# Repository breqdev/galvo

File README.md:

# Laser Vector Projector

Read the project writeup [here](https://breq.dev/projects/laser-projector)!

> This project is sponsored by PCBWay, who generously provided PCB fabrication services for this project. PCBWay provides high-quality boards with fast turnaround at low cost, and are a great option for both hobbyists and professionals.

Contained in this repository:

- [KiCAD Board Layout Files](board)
- [Bill of Materials](board/ESP32%20Galvo%20Driver.csv)
- [Firmware](galvo-firmware) -- you'll need to have the [Espressif toolchain](https://docs.espressif.com/projects/rust/book/getting-started/toolchain.html) installed to compile this
- [CAD files](cad) (SketchUp source files and STL)

Stuff not covered in the Bill of Materials:

- [RGB laser module and driver](https://www.aliexpress.us/item/3256810125144918.html)
- [Galvos with XY mount, driver, and power supply](https://www.aliexpress.us/item/3256809659931894.html)
- [Laser safety goggles](https://lasersafety.com/product/f42-p5l13-5000/)

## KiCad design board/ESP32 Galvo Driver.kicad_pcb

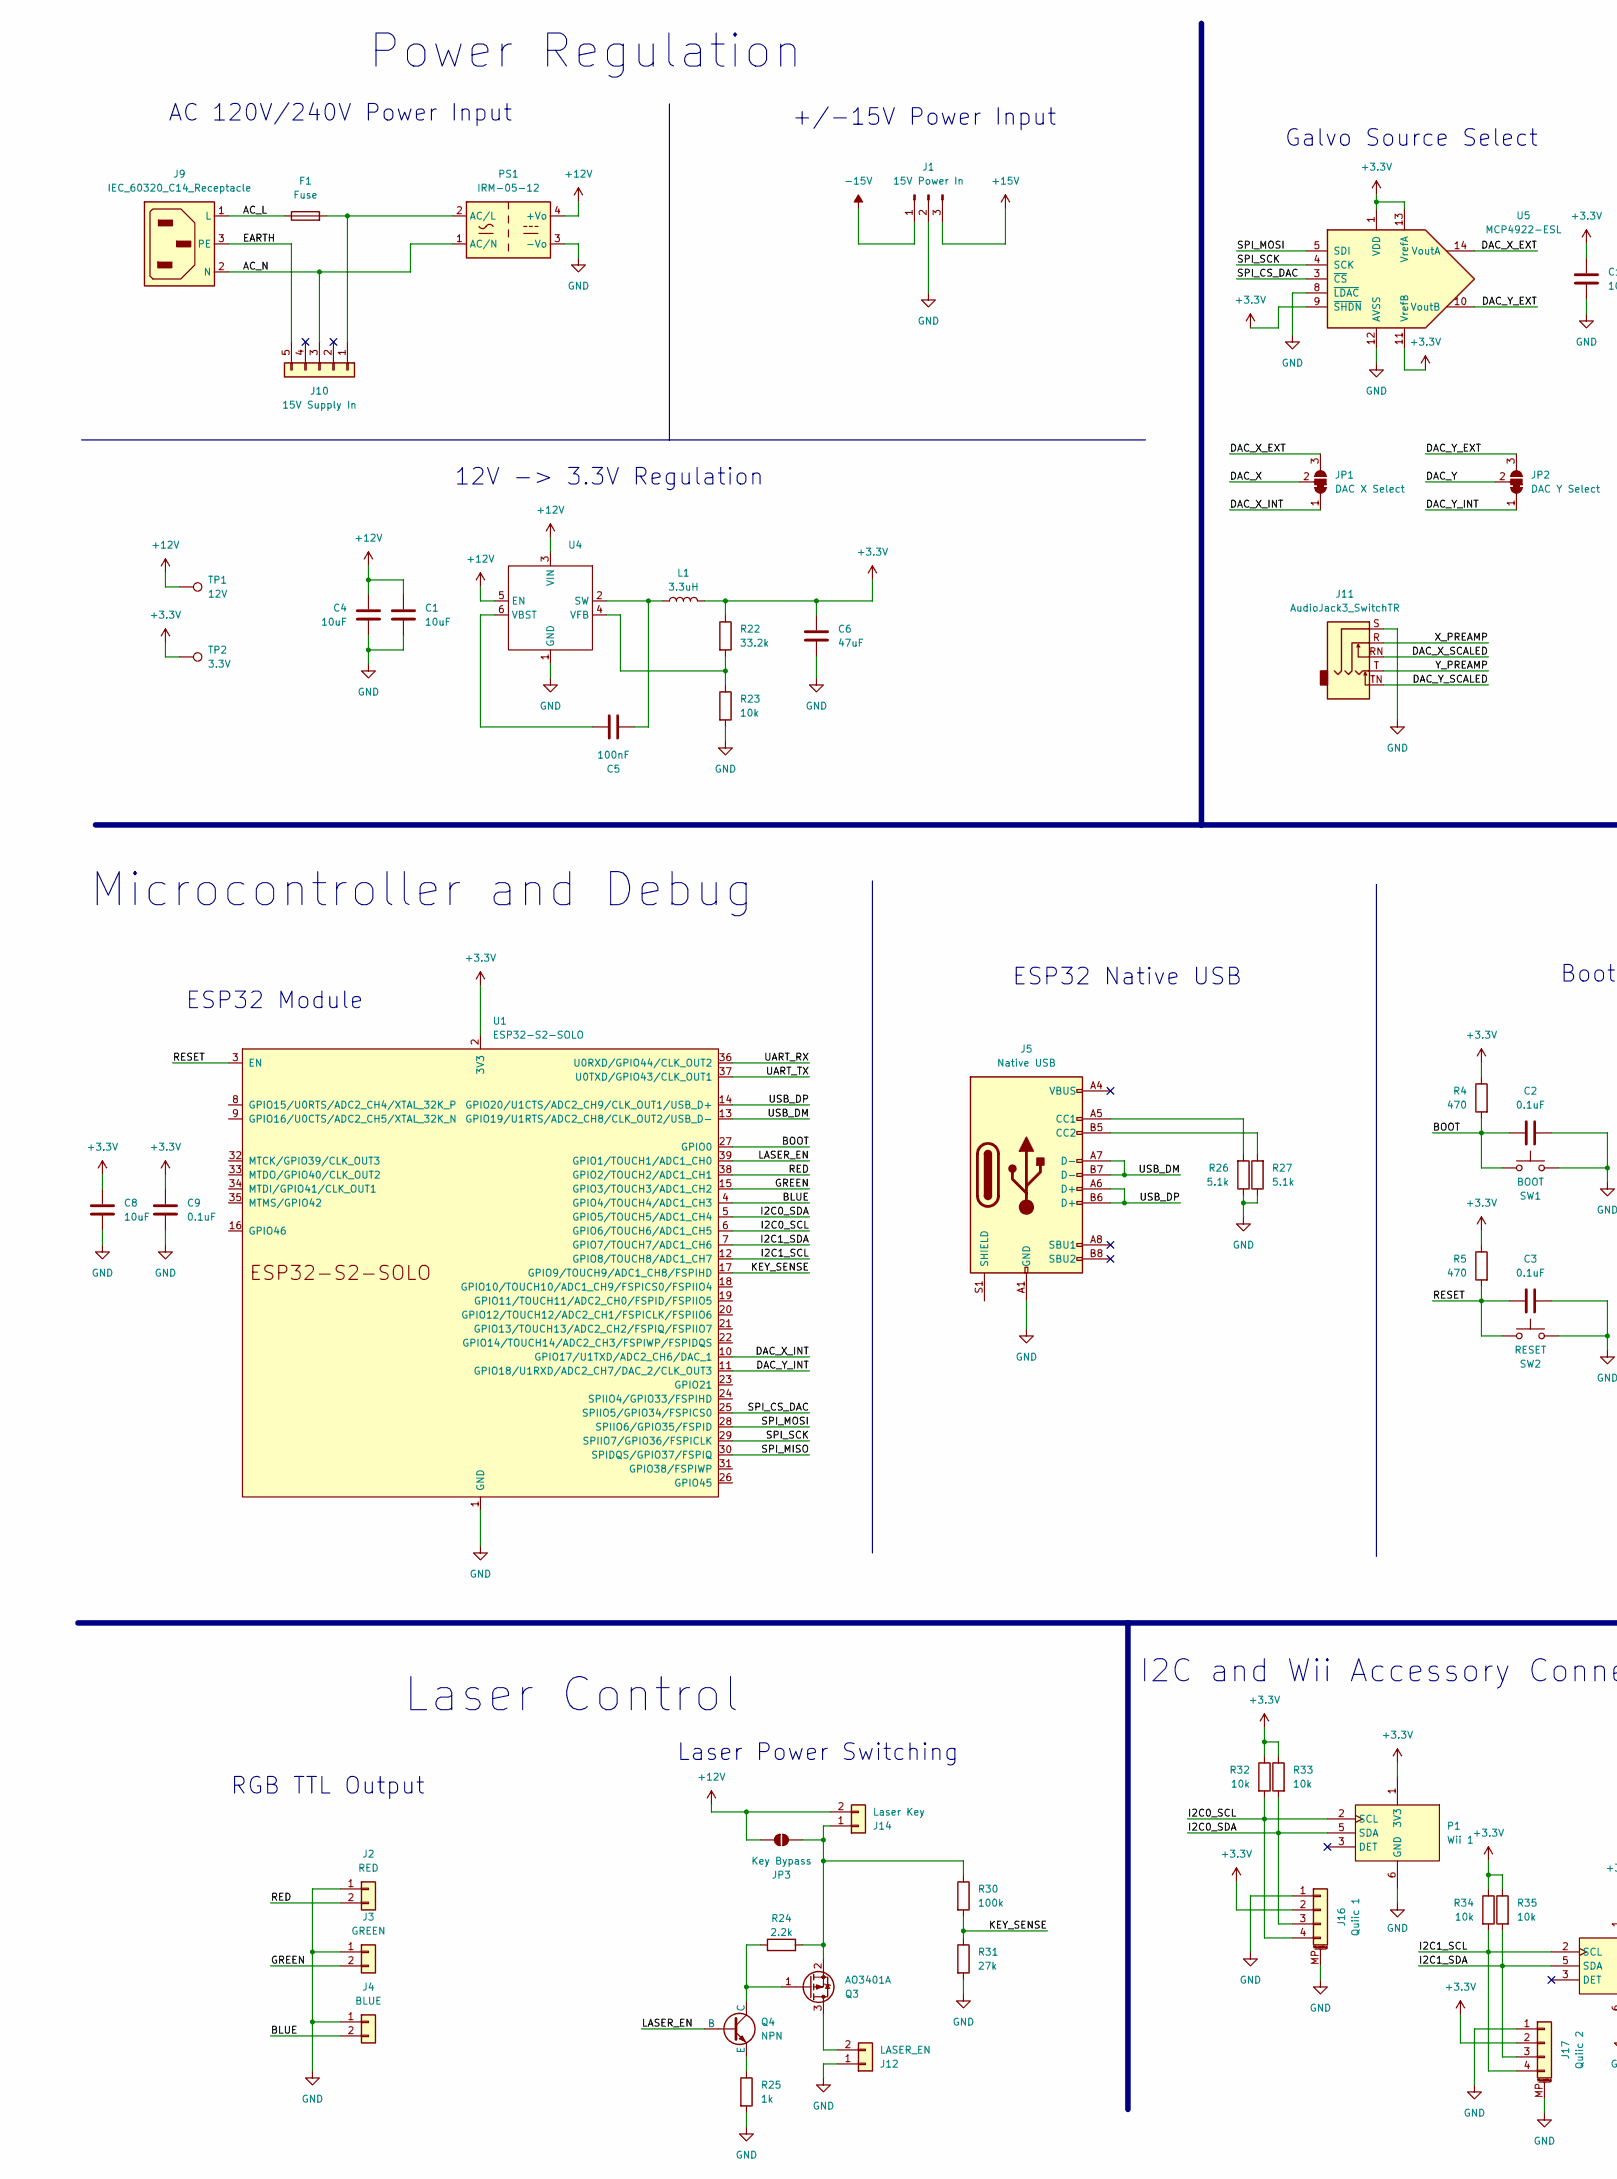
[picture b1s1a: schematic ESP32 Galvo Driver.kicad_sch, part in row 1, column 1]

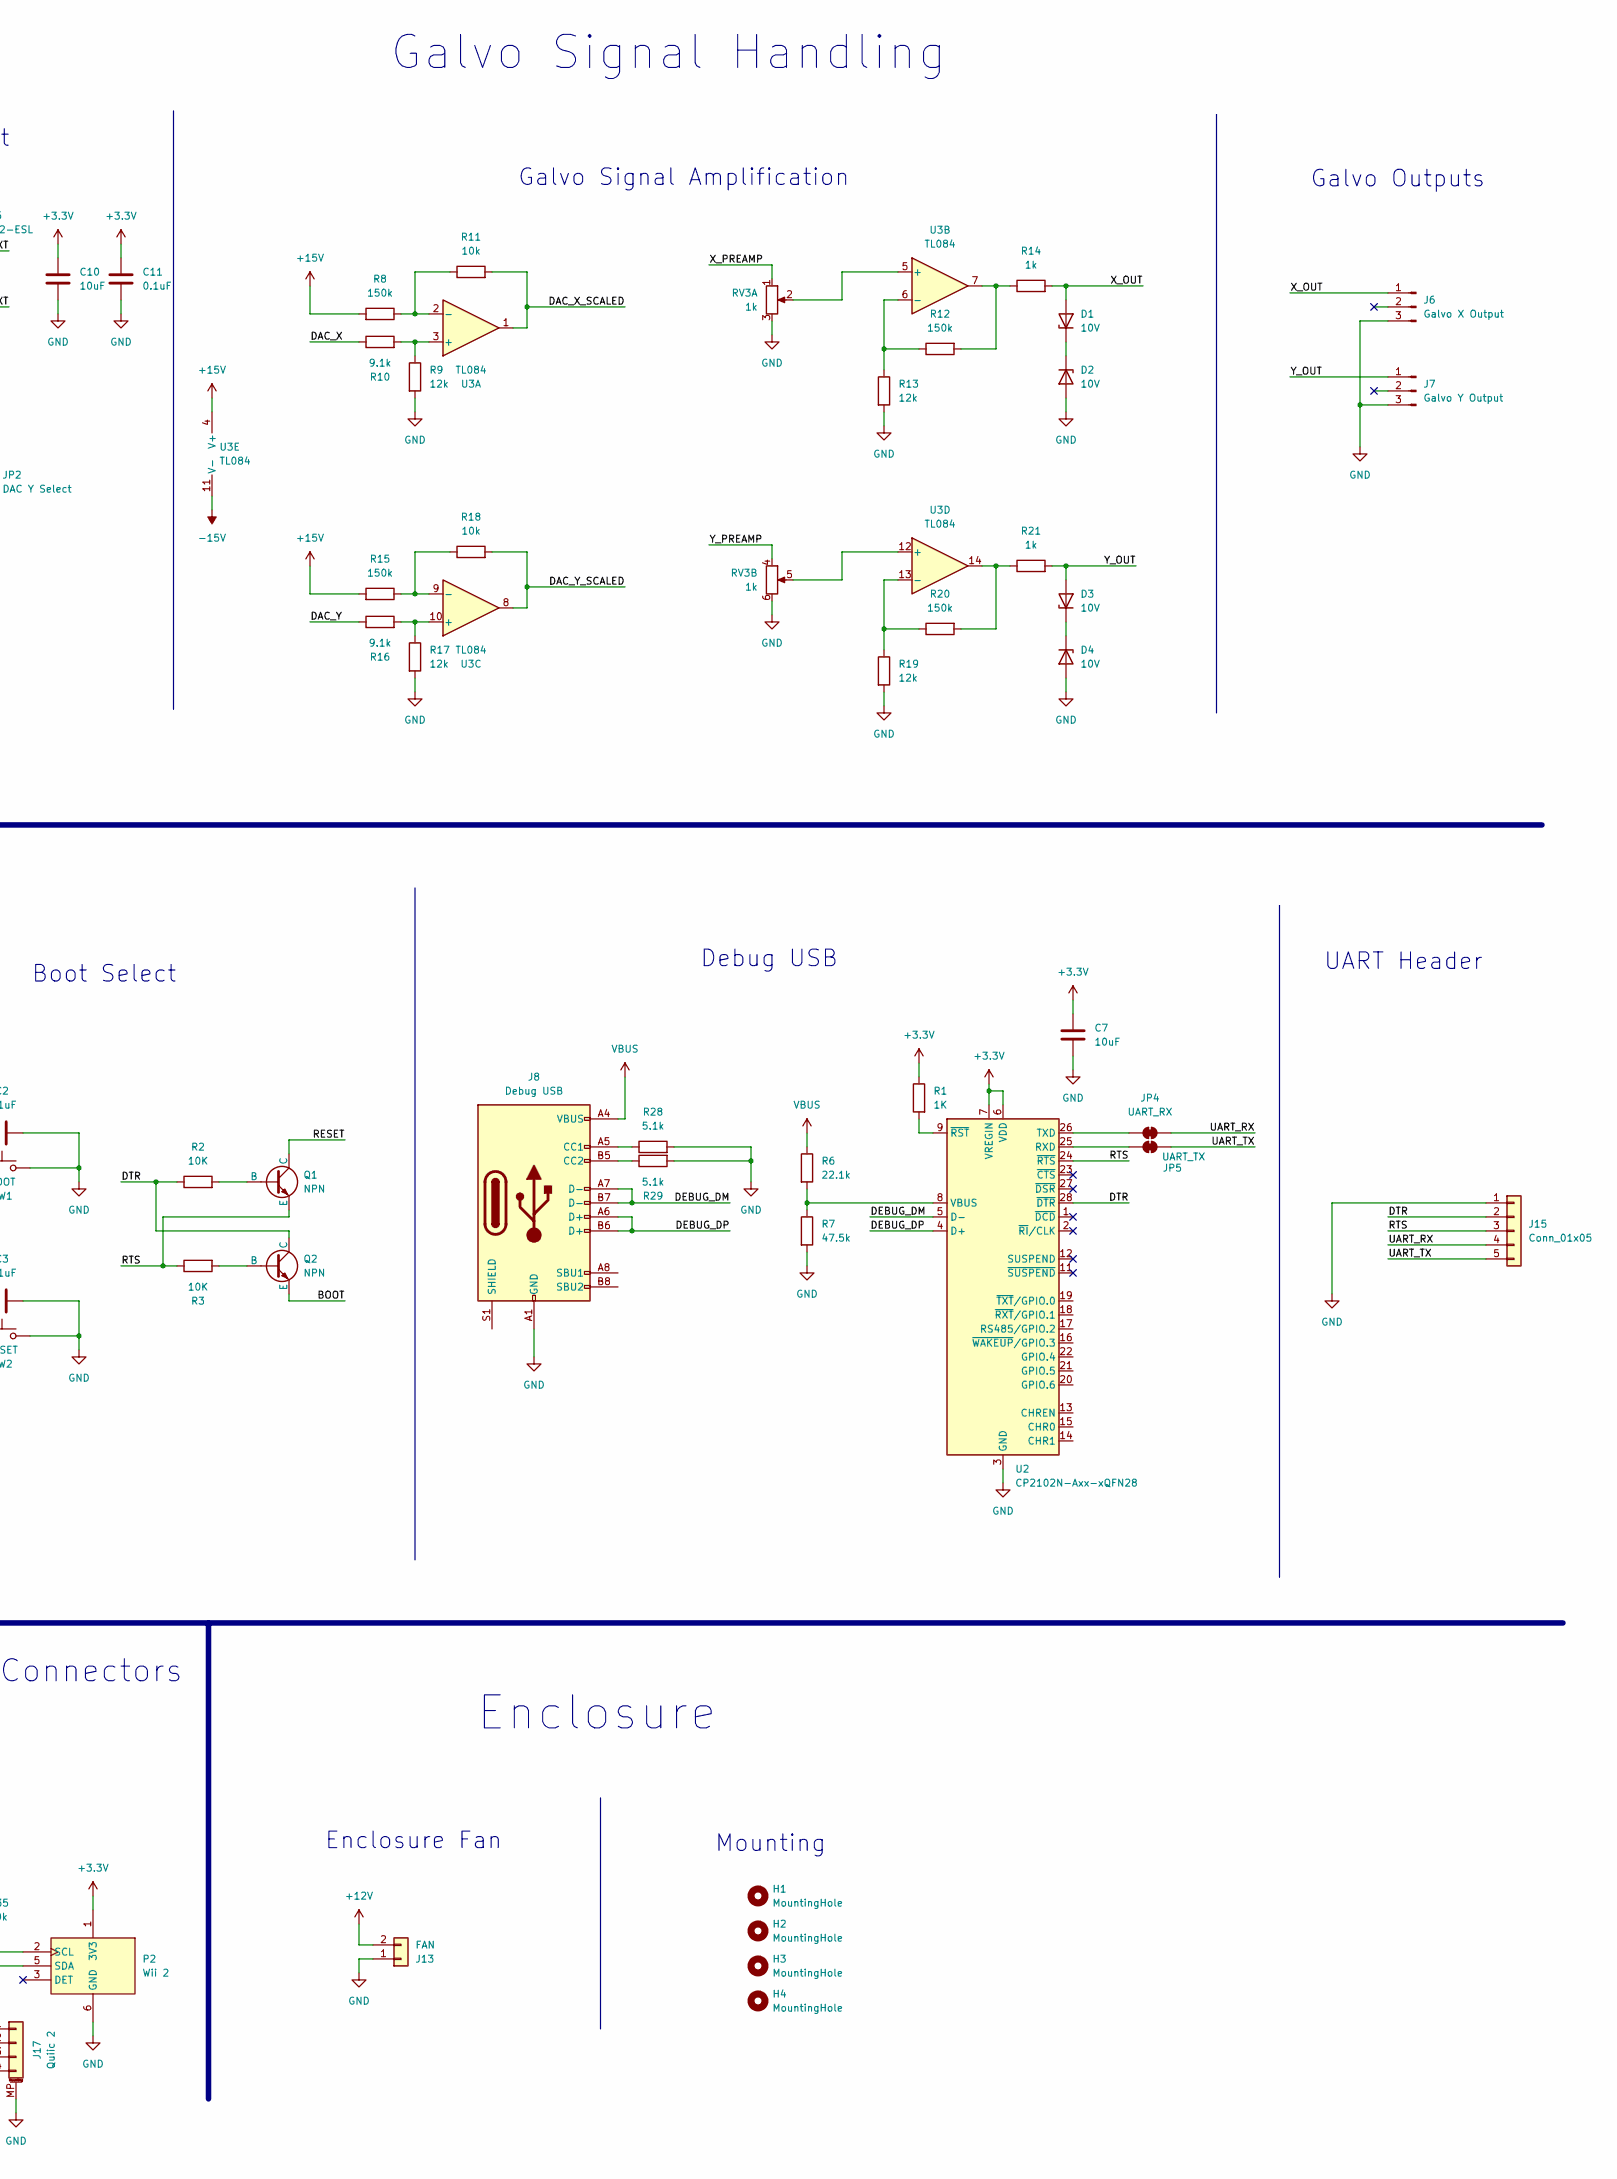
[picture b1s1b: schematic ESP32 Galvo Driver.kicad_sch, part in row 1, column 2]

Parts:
C1, C4, C7, C8, C10: 10uF; C_0603_1608Metric_Pad1.08x0.95mm_HandSolder
C2, C3, C9, C11: 0.1uF; C_0603_1608Metric_Pad1.08x0.95mm_HandSolder
C5: 100nF; C_0603_1608Metric_Pad1.08x0.95mm_HandSolder
C6: 47uF; C_0603_1608Metric_Pad1.08x0.95mm_HandSolder
D1, D2, D3, D4: 10V; D_SOD-123
F1: Fuse; Fuseholder_Clip-5x20mm_Littelfuse_111_Inline_P20.00x5.00mm_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
H1, H2, H3, H4: MountingHole; MountingHole_3.2mm_M3
J1: 15V Power In; Molex_KK-254_AE-6410-03A_1x03_P2.54mm_Vertical
J2: RED; JST_XH_B2B-XH-A_1x02_P2.50mm_Vertical
J3: GREEN; JST_XH_B2B-XH-A_1x02_P2.50mm_Vertical
J4: BLUE; JST_XH_B2B-XH-A_1x02_P2.50mm_Vertical
J5: Native USB; USB_C_Receptacle_GCT_USB4105-xx-A_16P_TopMnt_Horizontal
J6: Galvo X Output; JST_XH_B3B-XH-A_1x03_P2.50mm_Vertical
J7: Galvo Y Output; JST_XH_B3B-XH-A_1x03_P2.50mm_Vertical
J8: Debug USB; USB_C_Receptacle_GCT_USB4105-xx-A_16P_TopMnt_Horizontal
J9: IEC_60320_C14_Receptacle; QUALTEK_703W-00_52
J10: 15V Supply In; Molex_KK-396_5273-05A_1x05_P3.96mm_Vertical
J11: AudioJack3_SwitchTR; Jack_3.5mm_CUI_SJ1-3525N_Horizontal
J12: LASER_EN; JST_XH_B2B-XH-A_1x02_P2.50mm_Vertical
J13: FAN; JST_XH_B2B-XH-A_1x02_P2.50mm_Vertical
J14: Laser Key; JST_XH_B2B-XH-A_1x02_P2.50mm_Vertical
J15: Conn_01x05; PinHeader_1x05_P2.54mm_Vertical
J16: Quiic 1; JST_SH_BM04B-SRSS-TB_1x04-1MP_P1.00mm_Vertical
J17: Quiic 2; JST_SH_BM04B-SRSS-TB_1x04-1MP_P1.00mm_Vertical
JP1: DAC X Select; SolderJumper-3_P1.3mm_Bridged12_RoundedPad1.0x1.5mm
JP2: DAC Y Select; SolderJumper-3_P1.3mm_Bridged12_RoundedPad1.0x1.5mm
JP3: Key Bypass; SolderJumper-2_P1.3mm_Open_TrianglePad1.0x1.5mm
JP4: UART_RX; SolderJumper-2_P1.3mm_Bridged_Pad1.0x1.5mm
JP5: UART_TX; SolderJumper-2_P1.3mm_Bridged_Pad1.0x1.5mm
L1: 3.3uH; L_0805_2012Metric_Pad1.15x1.40mm_HandSolder
P1: Wii 1; Nintendo_Wii_Peripheral_5Pin_Card_edge
P2: Wii 2; Nintendo_Wii_Peripheral_5Pin_Card_edge
PS1: IRM-05-12; Converter_ACDC_MeanWell_IRM-05-xx_THT
Q1, Q2, Q4: NPN; SOT-23-3
Q3: AO3401A; SOT-23
R1: 1K; R_0603_1608Metric_Pad0.98x0.95mm_HandSolder
R2, R3: 10K; R_0603_1608Metric_Pad0.98x0.95mm_HandSolder
R4, R5: 470; R_0603_1608Metric_Pad0.98x0.95mm_HandSolder
R6: 22.1k; R_0603_1608Metric_Pad0.98x0.95mm_HandSolder
R7: 47.5k; R_0603_1608Metric_Pad0.98x0.95mm_HandSolder
R8, R12, R15, R20: 150k; R_0603_1608Metric_Pad0.98x0.95mm_HandSolder
R9, R13, R17, R19: 12k; R_0603_1608Metric_Pad0.98x0.95mm_HandSolder
R10, R16: 9.1k; R_0603_1608Metric_Pad0.98x0.95mm_HandSolder
R11, R18, R23, R32, R33, R34, R35: 10k; R_0603_1608Metric_Pad0.98x0.95mm_HandSolder
R14, R21, R25: 1k; R_0603_1608Metric_Pad0.98x0.95mm_HandSolder
R22: 33.2k; R_0603_1608Metric_Pad0.98x0.95mm_HandSolder
R24: 2.2k; R_0603_1608Metric_Pad0.98x0.95mm_HandSolder
R26, R27, R28, R29: 5.1k; R_0603_1608Metric_Pad0.98x0.95mm_HandSolder
R30: 100k; R_0603_1608Metric_Pad0.98x0.95mm_HandSolder
R31: 27k; R_0603_1608Metric_Pad0.98x0.95mm_HandSolder
RV3: 1k; Potentiometer_Alps_RK163_Dual_Horizontal
SW1: BOOT; SW_Tactile_SPST_Angled_PTS645Vx58-2LFS
SW2: RESET; SW_Tactile_SPST_Angled_PTS645Vx58-2LFS
TP1: 12V; TestPoint_Pad_D2.5mm
TP2: 3.3V; TestPoint_Pad_D2.5mm
U1: ESP32-S2-SOLO
U2: CP2102N-Axx-xQFN28; QFN-28-1EP_5x5mm_P0.5mm_EP3.35x3.35mm
U3: TL084; SOIC-14_3.9x8.7mm_P1.27mm
U4: SOT-23-6_Handsoldering
U5: MCP4922-ESL; SOIC-14_3.9x8.7mm_P1.27mm

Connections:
+3.3V: C6.1, C7.1, C8.1, C9.1, C10.1, C11.1, J16.2, J17.2, L1.2, P1.1 (3V3), P2.1 (3V3), R1.1, R4.1, R5.1, R22.1, R32.1, R33.1, R34.1, R35.1, TP2.1 (1_1), U1.2 (3V3), U2.6 (VDD), U2.7 (VREGIN), U5.1 (VDD), U5.9 (~SHDN), U5.11 (VrefB), U5.13 (VrefA)
+12V: C1.1, C4.1, J13.2, J14.2, JP3.1 (A), PS1.4 (+Vo), TP1.1 (1_1), U4.3 (VIN), U4.5 (EN)
+15V: J1.3, R8.2, R15.2, U3.4 (V+)
-15V: J1.1, U3.11 (V-)
/AC_L: F1.1, J9.1 (L)
/AC_N: J9.2 (N), J10.3, PS1.1 (AC/N)
/BLUE: J4.2, U1.4 (GPIO4/TOUCH4/ADC1_CH3)
/BOOT: C2.1, Q2.3 (E), R4.2, SW1.2, U1.27 (GPIO0)
/DAC_X: JP1.2 (C), R10.1
/DAC_X_EXT: JP1.3 (B), U5.14 (VoutA)
/DAC_X_INT: JP1.1 (A), U1.10 (GPIO17/U1TXD/ADC2_CH6/DAC_1)
/DAC_X_SCALED: J11.RN, R11.2, U3.1
/DAC_Y: JP2.2 (C), R16.1
/DAC_Y_EXT: JP2.3 (B), U5.10 (VoutB)
/DAC_Y_INT: JP2.1 (A), U1.11 (GPIO18/U1RXD/ADC2_CH7/DAC_2/CLK_OUT3)
/DAC_Y_SCALED: J11.TN, R18.2, U3.8
/DEBUG_DM: J8.A7 (D-), J8.B7 (D-), U2.5 (D-)
/DEBUG_DP: J8.A6 (D+), J8.B6 (D+), U2.4 (D+)
/DTR: J15.2, Q2.1 (C), R2.1, U2.28 (~DTR)
/EARTH: J9.3 (PE), J10.5
/GREEN: J3.2, U1.15 (GPIO3/TOUCH3/ADC1_CH2)
/I2C0_SCL: J16.4, P1.2 (SCL), R32.2, U1.6 (GPIO6/TOUCH6/ADC1_CH5)
/I2C0_SDA: J16.3, P1.5 (SDA), R33.2, U1.5 (GPIO5/TOUCH5/ADC1_CH4)
/I2C1_SCL: J17.4, P2.2 (SCL), R34.2, U1.12 (GPIO8/TOUCH8/ADC1_CH7)
/I2C1_SDA: J17.3, P2.5 (SDA), R35.2, U1.7 (GPIO7/TOUCH7/ADC1_CH6)
/KEY_SENSE: R30.2, R31.1, U1.17 (GPIO9/TOUCH9/ADC1_CH8/FSPIHD)
/LASER_EN: Q4.2 (B), U1.39 (GPIO1/TOUCH1/ADC1_CH0)
/RED: J2.2, U1.38 (GPIO2/TOUCH2/ADC1_CH1)
/RESET: C3.1, Q1.1 (C), R5.2, SW2.2, U1.3 (EN)
/RTS: J15.3, Q1.3 (E), R3.1, U2.24 (~RTS)
/SPI_CS_DAC: U1.25 (SPIIO5/GPIO34/FSPICS0), U5.3 (~CS)
/SPI_MISO: U1.30 (SPIDQS/GPIO37/FSPIQ)
/SPI_MOSI: U1.28 (SPIIO6/GPIO35/FSPID), U5.5 (SDI)
/SPI_SCK: U1.29 (SPIIO7/GPIO36/FSPICLK), U5.4 (SCK)
/UART_RX: J15.4, JP4.2 (B), U1.36 (U0RXD/GPIO44/CLK_OUT2)
/UART_TX: J15.5, JP5.2 (B), U1.37 (U0TXD/GPIO43/CLK_OUT1)
/USB_DM: J5.A7 (D-), J5.B7 (D-), U1.13 (GPIO19/U1RTS/ADC2_CH8/CLK_OUT2/USB_D-)
/USB_DP: J5.A6 (D+), J5.B6 (D+), U1.14 (GPIO20/U1CTS/ADC2_CH9/CLK_OUT1/USB_D+)
/X_OUT: D1.2 (A), J6.1, R14.2
/X_PREAMP: J11.R, RV3.1
/Y_OUT: D3.2 (A), J7.1, R21.2
/Y_PREAMP: J11.T, RV3.4
GND: C1.2, C2.2, C3.2, C4.2, C6.2, C7.2, C8.2, C9.2, C10.2, C11.2, D2.2 (A), D4.2 (A), J1.2, J2.1, J3.1, J4.1, J5.A1 (GND), J5.A12 (GND), J5.B1 (GND), J5.B12 (GND), J6.3, J7.3, J8.A1 (GND), J8.A12 (GND), J8.B1 (GND), J8.B12 (GND), J11.S, J12.1, J13.1, J15.1, J16.1, J16.MP (MountPin), J17.1, J17.MP (MountPin), P1.6 (GND), P2.6 (GND), PS1.3 (-Vo), R7.2, R9.2, R13.2, R17.2, R19.2, R23.2, R25.2, R26.1, R27.1, R28.2, R29.2, R31.2, RV3.3, RV3.6, SW1.1, SW2.1, U1.1 (GND), U1.40 (GND), U1.41 (GND), U2.3 (GND), U2.29 (GND), U4.1 (GND), U5.8 (~LDAC), U5.12 (AVSS)
unnamed: D1.1 (K), D2.1 (K)
unnamed: D3.1 (K), D4.1 (K)
unnamed: J5.A5 (CC1), R26.2
unnamed: J5.B5 (CC2), R27.2
unnamed: J8.A5 (CC1), R28.1
unnamed: J8.B5 (CC2), R29.1
unnamed: F1.2, J10.1, PS1.2 (AC/L)
unnamed: J12.2, Q3.3 (D)
unnamed: J14.1, JP3.2 (B), Q3.2 (S), R24.2, R30.1
unnamed: JP4.1 (A), U2.26 (TXD)
unnamed: JP5.1 (A), U2.25 (RXD)
unnamed: Q1.2 (B), R2.2
unnamed: Q2.2 (B), R3.2
unnamed: Q3.1 (G), Q4.1 (C), R24.1
unnamed: Q4.3 (E), R25.1
unnamed: R12.2, R14.1, U3.7
unnamed: R20.2, R21.1, U3.14
unnamed: R6.2, R7.1, U2.8 (VBUS)
unnamed: R1.2, U2.9 (~RST)
unnamed: R9.1, R10.2, U3.3 (+)
unnamed: R8.1, R11.1, U3.2 (-)
unnamed: RV3.2, U3.5 (+)
unnamed: R12.1, R13.1, U3.6 (-)
unnamed: R16.2, R17.1, U3.10 (+)
unnamed: R15.1, R18.1, U3.9 (-)
unnamed: RV3.5, U3.12 (+)
unnamed: R19.1, R20.1, U3.13 (-)
unnamed: C5.2, L1.1, U4.2 (SW)
unnamed: C5.1, U4.6 (VBST)
unnamed: R22.2, R23.1, U4.4 (VFB)
VBUS: J8.A4 (VBUS), J8.A9 (VBUS), J8.B4 (VBUS), J8.B9 (VBUS), R6.1

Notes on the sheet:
Power Regulation
Enclosure
ESP32 Native USB
Microcontroller and Debug
AC 120V/240V Power Input
12V -> 3.3V Regulation
UART Header
RGB TTL Output
Laser Power Switching
Galvo Signal Handling
Boot Select
ESP32 Module
Enclosure Fan
I2C and Wii Accessory Connectors
Mounting
Laser Control
Galvo Source Select
+/-15V Power Input
Debug USB
Galvo Signal Amplification
Galvo Outputs

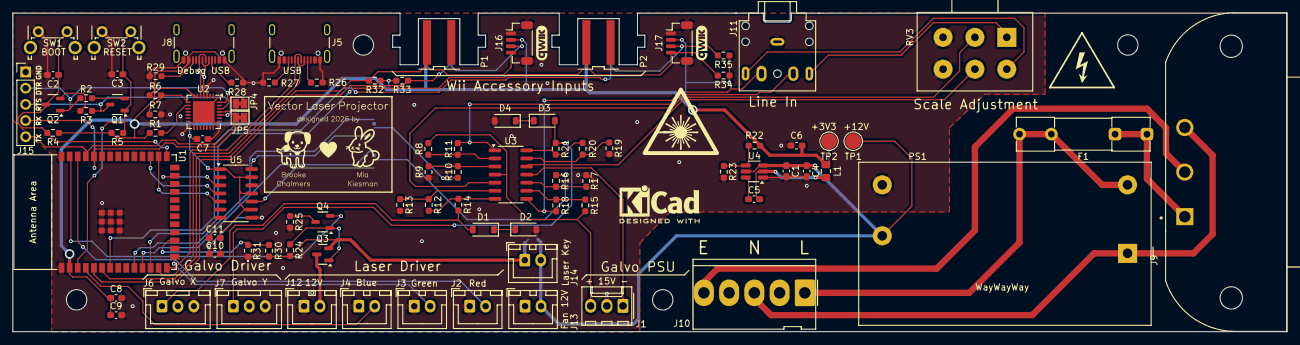
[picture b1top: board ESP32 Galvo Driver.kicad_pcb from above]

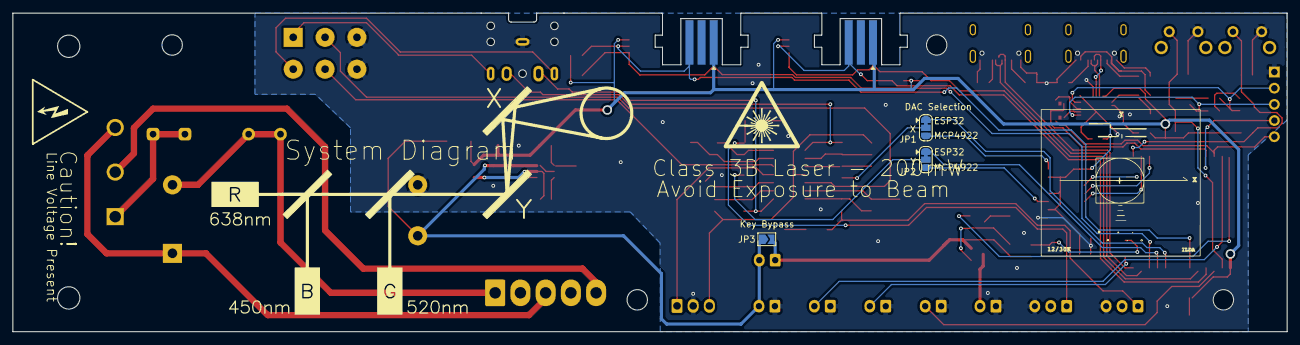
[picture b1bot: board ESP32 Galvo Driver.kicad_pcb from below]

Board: 2 copper layers, 199.9 x 50.0 mm, 95 parts (3 on the bottom side), 73 nets.

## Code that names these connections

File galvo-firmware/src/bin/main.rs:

#![no_std]
#![no_main]
#![deny(
    clippy::mem_forget,
    reason = "mem::forget is generally not safe to do with esp_hal types, especially those \
    holding buffers for the duration of a data transfer."
)]

use alloc::boxed::Box;
use alloc::string::String;
use alloc::vec::Vec;
use embassy_executor::Spawner;
use embassy_net::{DhcpConfig, StackResources};
use embassy_time::{Duration, Timer};
use esp_backtrace as _;
use esp_hal::clock::CpuClock;
use esp_hal::delay::Delay;
use esp_hal::i2c::master::{Config, I2c};
use esp_hal::ledc::timer::TimerIFace;
use esp_hal::ledc::{Ledc, LowSpeed, timer};
use esp_hal::otg_fs::{Usb, UsbBus};
use esp_hal::peripherals;
use esp_hal::rng::Rng;
use esp_hal::rtc_cntl::Rtc;
use esp_hal::time::Rate;
use esp_hal::timer::timg::TimerGroup;
use esp_radio::Controller;
use galvo_driver::controls::parse_report;
use galvo_driver::network::{
    RtcTimeSource, SharedRtc, connection, get_mastodon_status, get_time_ntp, net_task,
};
use galvo_driver::protocol::{Command, Response};
use usb_device::prelude::{UsbDeviceBuilder, UsbVidPid};
use usbd_serial::{SerialPort, USB_CLASS_CDC};
use vector_apps::apps::clock::Clock;
use vector_apps::apps::svg::SvgApp;
use vector_apps::apps::{self, Controls, VectorApp};
use wii_accessories::WiiAccessory;

use log::info;

use embassy_sync::blocking_mutex::Mutex;
use galvo_driver::lasers::Lasers;
use galvo_driver::led::IndicatorLed;
use vector_apps::apps::align::Align;
use vector_apps::apps::alphabet::AlphabetDemo;
use vector_apps::apps::asteroids::Asteroids;
use vector_apps::apps::cube::CubeDemo;
use vector_apps::apps::cycle::Cycle;
use vector_apps::apps::ilda::Ilda;
use vector_apps::apps::maps::Maps;

extern crate alloc;

// This creates a default app-descriptor required by the esp-idf bootloader.
// For more information see: <https://docs.espressif.com/projects/esp-idf/en/stable/esp32/api-reference/system/app_image_format.html#application-description>
esp_bootloader_esp_idf::esp_app_desc!();

// When you are okay with using a nightly compiler it's better to use https://docs.rs/static_cell/2.1.0/static_cell/macro.make_static.html
macro_rules! mk_static {
    ($t:ty,$val:expr) => {{
        static STATIC_CELL: static_cell::StaticCell<$t> = static_cell::StaticCell::new();
        #[deny(unused_attributes)]
        let x = STATIC_CELL.uninit().write(($val));
        x
    }};
}

static mut EP_MEMORY: [u32; 1024] = [0; 1024];

#[esp_rtos::main]
async fn main(spawner: Spawner) -> ! {
    // generator version: 1.0.1

    esp_println::logger::init_logger_from_env();

    let config = esp_hal::Config::default().with_cpu_clock(CpuClock::max());
    let peripherals = esp_hal::init(config);

    esp_alloc::heap_allocator!(#[esp_hal::ram(reclaimed)] size: 139264);

    let timg0 = TimerGroup::new(peripherals.TIMG0);
    esp_rtos::start(timg0.timer0);

    info!("Embassy initialized!");

    let delay = Delay::new();

    let ledc = Ledc::new(peripherals.LEDC);
    let mut timer = ledc.timer::<LowSpeed>(timer::Number::Timer0);
    timer
        .configure(timer::config::Config {
            duty: timer::config::Duty::Duty8Bit,
            clock_source: timer::LSClockSource::APBClk,
            frequency: Rate::from_khz(24),
        })
        .unwrap();

    let mut lasers = Lasers::new(
        peripherals.GPIO1,
        peripherals.GPIO9,
        peripherals.GPIO2,
        peripherals.GPIO3,
        peripherals.GPIO4,
        ledc,
        &timer,
        peripherals.DAC2,
        peripherals.GPIO18,
        peripherals.DAC1,
        peripherals.GPIO17,
    );

    let mut controls_p1 = {
        let i2c = I2c::new(peripherals.I2C0, Config::default())
            .unwrap()
            .with_sda(peripherals.GPIO5)
            .with_scl(peripherals.GPIO6);

        WiiAccessory::new(i2c)
    };
    let mut controls_p2 = {
        let i2c = I2c::new(peripherals.I2C1, Config::default())
            .unwrap()
            .with_sda(peripherals.GPIO7)
            .with_scl(peripherals.GPIO8);

        WiiAccessory::new(i2c)
    };

    let usb = Usb::new(peripherals.USB0, peripherals.GPIO20, peripherals.GPIO19);
    let usb_bus = UsbBus::new(usb, unsafe { &mut *core::ptr::addr_of_mut!(EP_MEMORY) });

    let mut serial = SerialPort::new(&usb_bus);

    let mut usb_dev = UsbDeviceBuilder::new(&usb_bus, UsbVidPid(0x303A, 0x3001))
        .device_class(USB_CLASS_CDC)
        .build();

    let rtc = mk_static!(SharedRtc, Mutex::new(Rtc::new(peripherals.LPWR)));

    let esp_radio_ctrl = &*mk_static!(Controller<'static>, esp_radio::init().unwrap());

    let (controller, interfaces) =
        esp_radio::wifi::new(esp_radio_ctrl, peripherals.WIFI, Default::default()).unwrap();

    let wifi_interface = interfaces.sta;

    let mut dhcp_options: DhcpConfig = Default::default();
    dhcp_options.hostname = Some(heapless::String::try_from("laser-esp32").unwrap());
    let config = embassy_net::Config::dhcpv4(dhcp_options);

    let rng = Rng::new();
    let seed = (rng.random() as u64) << 32 | rng.random() as u64;

    // Init network stack
    let (stack, runner) = embassy_net::new(
        wifi_interface,
        config,
        mk_static!(StackResources<8>, StackResources::<8>::new()),
        seed,
    );

    spawner.spawn(connection(controller)).ok();
    spawner.spawn(net_task(runner)).ok();

    info!("Waiting for network...");

    stack.wait_config_up().await;

    // get_time_ntp(&stack, rtc).await;

    // let post = get_mastodon_status(&stack).await;

    let mut serial_buffer: [u8; 2048] = [0; 2048];
    let mut serial_rx_length: usize = 0;

    let mut apps: Vec<Box<dyn VectorApp>> = Vec::with_capacity(5);
    apps.push(Box::new(AlphabetDemo::new(String::from(
        "Hershey Goth Engbreq.dev",
        // "  KiCad  NewStroke breq.dev",
    ))));
    // apps.push(Box::new(CubeDemo::new()));
    // apps.push(Box::new(Asteroids::new()));
    // apps.push(Box::new(Maps::new()));
    // apps.push(Box::new(SvgApp::new()));
    // apps.push(Box::new(Ilda::new()));
    apps.push(Box::new(Align::new()));
    // apps.push(Box::new(Clock::new(RtcTimeSource::new(rtc))));

    let mut active_demo: Box<dyn apps::VectorApp> = Box::new(Cycle::new(apps));
    // let mut active_demo: Box<dyn apps::VectorApp> = Box::new(Asteroids::new());

    let mut frameno: u64 = 0;

    info!("Galvo system initialized!");

    loop {
        if usb_dev.poll(&mut [&mut serial]) {
            let mut buf = [0u8; 64];

            if let Ok(count) = serial.read(&mut buf)
                && count > 0
            {
                // Append to RX buffer
                if serial_rx_length + count <= serial_buffer.len() {
                    serial_buffer[serial_rx_length..serial_rx_length + count]
                        .copy_from_slice(&buf[..count]);
                    serial_rx_length += count;
                }

                // Look for newline delimiter
                if let Some(pos) = serial_buffer[..serial_rx_length]
                    .iter()
                    .position(|&b| b == b'\n')
                {
                    let json_bytes = &serial_buffer[..pos];

                    if let Ok(s) = core::str::from_utf8(json_bytes)
                        && let Ok(cmd) = serde_json::from_str::<Command>(s)
                    {
                        match cmd {
                            Command::SetIndicatorLight { r, g, b } => {
                                // indicator.set_color(smart_leds::RGB { r, g, b });
                            }
                        }

                        let result = Response { success: true };

                        let response = serde_json::to_string(&result).unwrap();
                        let _ = serial.write(response.as_bytes());
                    }

                    // Remove processed message
                    let remaining = serial_rx_length - (pos + 1);
                    serial_buffer.copy_within(pos + 1..serial_rx_length, 0);
                    serial_rx_length = remaining;
                }
            }
        }

        // if lasers.is_interlock_active() {
        //     info!("Key in ON position");
        // } else {
        //     info!("Key in OFF position");
        // }

        if frameno % 4 == 0 {
            let player_1 = parse_report(controls_p1.get_input());
            let player_2 = parse_report(controls_p2.get_input());
            // info!("controls state: {:?}", controls);
            let merged = player_1.merge(player_2);
            active_demo.handle_controls(merged);
        }

        frameno += 1;

        for p in active_demo.get_path(frameno) {
            // Output coordinates
            lasers.display(p);

            // DAC/galvo settling time
            delay.delay_micros(p.delay as u32);
        }

        // yield to other tasks
        Timer::after(Duration::from_millis(1)).await;
    }
}

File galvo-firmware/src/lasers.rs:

use esp_hal::analog::dac::Dac;
use esp_hal::gpio::interconnect::PeripheralOutput;
use esp_hal::gpio::{
    DriveMode, Input, InputConfig, InputPin, Level, Output, OutputConfig, OutputPin,
};
use esp_hal::ledc::channel::{Channel, ChannelHW, ChannelIFace};
use esp_hal::ledc::timer::Timer;
use esp_hal::ledc::{LSGlobalClkSource, Ledc, LowSpeed, channel};
use esp_hal::peripherals::{DAC1, DAC2, GPIO17, GPIO18};

use vector_apps::point::Point;

pub struct Lasers<'a> {
    enable: Output<'a>,
    interlock: Input<'a>,
    red: Channel<'a, LowSpeed>,
    green: Channel<'a, LowSpeed>,
    blue: Channel<'a, LowSpeed>,
    x: Dac<'a, DAC2<'a>>,
    y: Dac<'a, DAC1<'a>>,
}

impl<'a> Lasers<'a> {
    pub fn new(
        enable: impl OutputPin + 'a,
        interlock: impl InputPin + 'a,
        red: impl PeripheralOutput<'a>,
        green: impl PeripheralOutput<'a>,
        blue: impl PeripheralOutput<'a>,
        mut ledc: Ledc<'a>,
        timer: &'a Timer<'a, LowSpeed>,
        dac_x: DAC2<'a>,
        pin_x: GPIO18<'a>,
        dac_y: DAC1<'a>,
        pin_y: GPIO17<'a>,
    ) -> Self {
        ledc.set_global_slow_clock(LSGlobalClkSource::APBClk);

        let en_output = Output::new(enable, Level::Low, OutputConfig::default());
        let interlock_input = Input::new(interlock, InputConfig::default());

        let mut red_ch = ledc.channel(channel::Number::Channel0, red);
        red_ch
            .configure(channel::config::Config {
                timer,
                duty_pct: 10,
                drive_mode: DriveMode::PushPull,
            })
            .unwrap();

        let mut green_ch = ledc.channel(channel::Number::Channel1, green);
        green_ch
            .configure(channel::config::Config {
                timer,
                duty_pct: 10,
                drive_mode: DriveMode::PushPull,
            })
            .unwrap();

        let mut blue_ch = ledc.channel(channel::Number::Channel2, blue);
        blue_ch
            .configure(channel::config::Config {
                timer,
                duty_pct: 10,
                drive_mode: DriveMode::PushPull,
            })
            .unwrap();

        Self {
            enable: en_output,
            interlock: interlock_input,
            red: red_ch,
            green: green_ch,
            blue: blue_ch,
            x: Dac::new(dac_x, pin_x),
            y: Dac::new(dac_y, pin_y),
        }
    }

    pub fn is_interlock_active(&self) -> bool {
        self.interlock.is_high()
    }

    pub fn display(&mut self, p: &Point) {
        self.enable.set_high();

        self.x.write(255 - p.x);
        self.y.write(255 - p.y);
        self.red.set_duty_hw(p.color.0 as u32);
        self.green.set_duty_hw(p.color.1 as u32);
        self.blue.set_duty_hw(p.color.2 as u32);
    }
}

impl<'a> Drop for Lasers<'a> {
    fn drop(&mut self) {
        self.enable.set_low();
    }
}

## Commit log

2026-01-15 initial import
2026-01-16 demo for both sim and real
2026-01-16 remove extra vec copy
2026-01-16 build script for hershey fonts
2026-01-16 better tuning for text display
2026-01-19 asteroids!
2026-01-19 basic map fetching and rendering
2026-01-19 working map drawing
2026-01-23 improvements to map drawing and asteroids
2026-01-24 working ntp clock!
2026-01-24 refactor networking code
2026-01-24 24-bit color support!
2026-01-24 mastodon post fetching demo
2026-01-24 basic interface for controls input
2026-01-24 basic controls for asteroids
2026-01-24 support for color gradients
2026-01-24 cleanup, refactor shared math functions
2026-01-24 use standard add and mul traits
2026-01-24 migrate roads cropping to rust
2026-01-24 add controls for moving the map around
2026-01-24 clippy lint and stuff
2026-02-08 add board!
2026-02-13 ILDA test pattern WIP
2026-02-14 update board
2026-02-14 add newstroke font renderer
2026-02-14 ilda rate changes
2026-02-14 ilda: fix scaling
2026-02-21 gtfs, litt.chr parsing
2026-02-21 remove CJK from newstroke data
2026-03-14 switch to pinouts from PCB, separate package for vector text
2026-03-15 move wii accessory driver to separate crate
2026-04-06 lots of fun stuff! colorful roads, better asteroids
2026-04-07 optimizations!
2026-05-04 final code for taking pictures
2026-06-11 board updates: fix improper wiring of AC input
2026-06-11 add BOM
2026-06-11 import CAD and add readme
